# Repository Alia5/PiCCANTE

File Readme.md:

<br />

[![Discord](https://img.shields.io/discord/368823110817808384?logo=discord&logoColor=white&label=Discord&color=%23535fe5
)](https://discord.gg/hs34MtcHJY)

# PiCCANTE 🌶️

**Pi**CCANTE **C**ar **C**ontroller **A**rea **N**etwork **T**ool for **E**xploration

PiCCANTE is a powerful hacking tool for accessing, exploring, and manipulating vehicle CAN bus networks, built on the affordable Raspberry Pi Pico platform. Designed for researchers, security professionals, and automotive enthusiasts looking to dive deep into vehicle systems without expensive proprietary equipment.

⚠️ **Always exercise caution when connecting to vehicle systems.** ⚠️ 

## ℹ️ About PiCCANTE

PiCCANTE is designed to be a dead-**simple**, dirt-**cheap**, and readily-**available** hardware platform for vehicle research and exploration.  
As cars become more and more computerized, manufacturers keep locking them behind proprietary tools and restrictive systems, even connect vehicles to the internet, yet they still rely on communication standards from the 1980s.  
Car hacking and independent research grows increasingly important to discover security vulnerabilities, reverse engineer vehicle systems, and empower owners with custom tools for diagnostics and tuning that support the Right to Repair movement.

The project leverages Raspberry Pi Pico (2 [W]) development boards, selected for their exceptional affordability, global availability, impressive specifications, and well-documented open-source SDK.

### 🎯 Core Goals

<sub>Keep it D.I.R.T.Y 😉</sub>  

- **D**ead-Simple 🔨  
  - Simple enough for perfboard soldering with minimal components. (Proper PCB available!)
  - No fiddling around with compilers and SDKs: Pre-built firmware releases for immediate use.
- **I**nexpensive 💰  
  - Minimal hardware requirements to keep costs dirt-cheap.  
  - Based on affordable, off-the-shelf components.
- **R**eadily-Available 🌎
  - Fully open-source hardware and software.  
  - Uses widely available Raspberry Pi Pico boards.
- **T**ool-Compatible 🔌
  - Seamless integration with existing CAN tools.  
- **Y**our-First Choice 💡
  - Driverless across all major operating systems.  
  - Easy to use for beginners and experts alike.
  - 🔜 Documentation

### ✨ Features

- ✅ Up to 3× CAN 2.0B interfaces (2× on RP2040 (Pico[W]), 3× on RP2350 (Pico 2[W]))
- ✅ 1× USB-CDC PiCCANTE command + GVRET (binary only) interface
  - Compatible with [SavvyCAN](https://github.com/collin80/SavvyCAN) and other automotive tools
- ✅ Up to 3× USB-CDC SLCAN interfaces (dedicated to each CAN channel)
  - SocketCAN compatible via [can-utils (Linux)](https://github.com/linux-can/can-utils)
- ✅ LED status indicators
- ✅ Command line interface for configuration and diagnostics
- ✅ Auto (Deep) sleep on idle + Wakeup on CAN activity.
- ✅ WiFi support (on Pico W models)
  - ✅ Create WiFi access point (`wifi ap <ssid> <password> <channel>`)
  - ✅ Connect to existing WiFi networks (`wifi connect <ssid> <password>`)
  - ✅ WiFi status and configuration commands
  - ✅ PiCCANTE configuration + GVRET interface as Telnet server
- ✅ Web-based configuration interface (on Pico W models)
  - ✅ Fully responsive on desktop and mobile
  - ✅ Full device configuration
  - ✅ Device Monitoring
  - 🔜 Integrated Web CLI:  
    - 🔜 Live CAN-bus monitoring
    - 🔜 ELM327 commands
  - 🔜 MITM mode configuration
- ✅ Bluetooth support (on Pico W models)
- ☑️ (partial) ELM327 emulator
  - ☑️ Partially implemented AT command set
    - Setup up CAN bus, auto protocol detection and filters (🔜) are missing.  
      Configure the CAN bus beforehand - this is a hacking-tool, you should now your vehicles CAN bus settings.
  - ✅ Support for USB, Bluetooth or WiFi communication
  - ✅ PID request and response
    - ✅ 11bit and 29bit addressing
    - ✅ Multi-Frame PID support (ISO-TP)
    - ✅ Fast mode when number of answered frames is known
  - ✅ Report vehicle battery voltage (if ADC is connected)
  - 🔜 Adaptive Timeouts
- ✅ 3D printable case designs for creating PiCCANTE based OBD-II dongles
- 🔜 Data logging to SD card
- 🔜 MITM mode for advanced analysis / vehicle tuning
- 🔜 (Software) CAN filters

## 🔧 Hardware

For more information, checkout the [hardware](./hardware) directory.

### Simplest version

PiCCANTE is designed to be modular and can be built with just a few components.  
The simplest version just uses a Pico board and a CAN transceiver.

### 🛒 What You'll Need

- 1× Raspberry Pi Pico (any model, RP2040 or RP2350)
  - **Note:** The Pico 2 W (RP2350) is recommended for full feature support, including WiFi and Bluetooth.
- 1-3× CAN transceivers (readily available SN65HVD or any other 3.3V compatible transceiver)
  - **Note:** ⚠️ Most readily available transceiver breakout-boards have a 120 Ohm terminating Resistor on them, when connecting to an existing (terminated) CAN bus this **needs** to be removed. ⚠️
- USB cable

If you want more features, you can add an SD card slot, a buck converter, and other things.

<details>
  <summary>Show Details</summary>
  <br />

</details>

### OBD-II Dongle (DIY Perfboard)

A full PiCCANTE based OBD-II dongle is simple enough to be soldered onto double-sided perfboard.

<details>
  <summary>Show Details</summary>
<br />

A perfboard version fits on a 60mm x 50mm board and the 3D printable case measures just 97mm x 56mm including the OBD-II connector.

It cam be built with the following components (but you can omit anything you don't need):

- Pi Pico (2 [W])
- 3x CAN transceivers (eg. SN65HVD, any 3.3V compatible transceiver will do)
- buck-converter
- SD card slot
- Voltage divider for measuring the vehicle's battery voltage
- Schottky diode for safe dual power supply (1N5817)
- **Case**:
  - ABS/ASA or PETG filament
  - 3x M3 screws
  - 3x M3 heatset inserts
  - 1x male OBD-II connector (I used [this one](https://store.minitools.com/en/components-and-connectors/obd-connectors/sep-a-obd-e2-obd2-male-connector.html))
  - Wires

</details>

### OBD-II Dongle (Manufactured PCB)

A proper PCB with better CAN transceivers can be found in the [hardware directory](./hardware/PiCCANTE-OBD-Dongle/PCB).  
It is made with [KiCAD](https://www.kicad.org/) and can be manufactured by any PCB manufacturer.

<details>
  <summary>Show Details</summary>
    <br />

</details>

## 💾 Software

Pre-compiled binaries for all official Raspberry Pi Pico boards are available as CI action artifacts in the GitHub repository.

When connected via USB, PiCCANTE exposes **up to** 4× USB-CDC interfaces:

- 1× Combined PiCCANTE command + GVRET (binary) interface
  - Always the _first_ exposed CDC device.
  - Also exposed via telnet if enabled on WiFi enabled boards.
- **Up to** 3× SLCAN interfaces (dedicated to each CAN channel)

### 🚀 Basic Usage Examples

#### 🐧 Linux with can-utils (slcan)

```bash
# Set up SLCAN interface
sudo slcand -o -s6 -t hw -S 3000000 /dev/ttyACM1 can0
sudo ip link set up can0

# Monitor CAN traffic
candump can0
```

#### 🖥️ Cross Platform with SavvyCAN

1. Connect PiCCANTE to USB
2. Open SavvyCAN
3. Go to Connection ➡️ Open Connection Window ➡️ Add device Connection
4. Select "Serial Connection (GVRET)" and choose the appropriate COM port / TTY
5. Click "Create New Connection"

### ⌨️ PiCCANTE Commands

```
atz             - Enable ELM mode (if ELM327-Emulator is on USB)
binary          - Toggle GVRET binary mode (binary <on|off>)
can_bitrate     - Change CAN bus bitrate (can_bitrate <bus> <bitrate>)
can_disable     - Disable CAN bus (can_disable <bus>)
can_enable      - Enable CAN bus with specified bitrate (can_enable <bus> <bitrate>)
can_status      - Show status of CAN buses
echo            - Toggle command echo (echo <on|off>)
elm             - Configure ELM327 interface and mode (elm <usb|bt PIN|wifi>  <can0|can1|can2>)
help            - Display this help message
idle_timeout    - Set idle timeout in minutes (idle_timeout disable|<minutes>)
led_mode        - Set LED mode (led_mode <0-3>) 0=OFF, 1=Power, 2=CAN Activity
log_level       - Set log level (log_level <0-3>). 0=DEBUG, 1=INFO, 2=WARNING, 3=ERROR
reset           - Reset the system (reset)
save            - Save current settings to flash
set_num_busses  - Set number of CAN buses (can_num_busses [number])
settings        - Show current system settings
sleep           - Enter deep sleep mode (sleep)
sys_stats       - Display system information and resource usage (sys_stats [cpu|heap|fs|tasks|uptime|adc|wifi])
telnet          - Enable or disable Telnet and set port (telnet enable|disable | telnet <port
version         - Display version information (version)
wifi            - Manage WiFi settings (wifi info | wifi connect <ssid> <password> | wifi ap <ssid> <password> <channel> | wifi disable)
```

## ❓ Frequently Asked Questions

### 🔄 Why only CAN2.0B and not CAN FD/XL?

The Raspberry Pi Pico has no native CAN support. The PIO can2040 implementation we're using only supports CAN 2.0B (due to licensing issues).  
However, if you **need** CAN FD or other bus types, feel free to open a PR supporting a CAN controller (like MCP2518FD).  

### 🔌 Can I use PiCCANTE with Linux/Windows/macOS?

Yes! PiCCANTE is designed to be cross-platform. It works with any operating system as a standard USB device with no special drivers required.  
For SLCAN interfaces, Linux users can use can-utils to provide a SocketCAN interface, while all platforms support the GVRET/SLCAN interface through tools like SavvyCAN.

### 💻 How many CAN buses can I monitor simultaneously?

Up to 3 CAN buses on the RP2350 (Pico 2/2W) and up to 2 CAN buses on the RP2040 (original Pico/Pico W).  
Each bus has a dedicated USB-CDC SLCAN interface.

### 🔧 Why build my own instead of buying a commercial CAN adapter?

PiCCANTE gives you a fully open-source solution at a fraction of the cost of commercial tools.  
You get complete control over the hardware and software, the ability to customize for specific needs, and valuable learning experience about CAN networks and embedded systems.

## ❓ Troubleshooting

- **Issue**: CAN bus not receiving data  
  *Solutions*:  
  - Verify CAN status with `can_status` command
  - Verify wiring and bitrate settings
  - Check for proper bus termination resistance (remove resistor on the transceiver if connected to an existing CAN-bus)

- **Issue**: LED not lighting up / blinking  
  *Solutions*:
  - Check USB connection and power
  - Check led_mode command on the first USB CDC device

## 🛠️ Development

PiCCANTE is built using the Raspberry Pi Pico SDK and follows standard Pico development practices. This section covers how to set up your development environment, build the project, and extend its functionality.

### 🧰 Prerequisites

- [Raspberry Pi Pico SDK](https://github.com/raspberrypi/pico-sdk)
- [CMake](https://cmake.org/) (3.13 or newer) [Windows: bundled with PicoSDK]
- C/C++ compiler (GCC ARM) [Windows: bundled with PicoSDK]
- [Visual Studio Code](https://code.visualstudio.com/) with the [Pico extension]([https://marketplace.visualstudio.com/items?itemName=marus25.cortex-debug](https://marketplace.visualstudio.com/items?itemName=raspberry-pi.raspberry-pi-pico)) (recommended)

### 🔄 Environment Setup

1. **Install the Pico SDK**:

    Follow the instructions in the [Pico SDK documentation](https://github.com/raspberrypi/pico-sdk) to install the SDK

2. **Clone PiCCANTE**:

    ```bash
    git clone git@github.com:Alia5/PiCCANTE.git
    cd PiCCANTE
    git submodule update --init --recursive
    ```

### 🏗️ Building

#### 💻 Command Line

1. **Configure with CMake**:

   ```bash
   cmake -B build -G Ninja -DCMAKE_BUILD_TYPE=Release
   ```

2. **Build the project**:

   ```bash
   cmake --build build --config Release
   ```

#### 🖥️ Using VS Code

1. Open the PiCCANTE folder in VS Code
2. Press F1 and select "CMake: Configure"
3. Press F7 to build the project
4. To flash, connect a Pico in BOOTSEL mode and press F5

## 👥 Contributing

Contributions to PiCCANTE are welcome! Whether it's bug reports, feature requests, documentation improvements, or code contributions, your help makes this project better.

- **Bug Reports**: Open an issue describing the problem and steps to reproduce it
- **Feature Requests**: Open an issue describing the desired functionality
- **Code Contributions**: Fork the repository, make your changes, and submit a pull request

### Extending PiCCANTE

PiCCANTE is designed to be extensible. Here are some key areas where you might want to extend functionality:

- **Adding new commands**: Extend the command interpreter to add custom commands.
- **Implementing new protocols**: Add new protocol handlers in their respective directories.
- **Car-specific tools**: Fork PiCCANTE to create a car-specific tool and diagnostics dongle.
- **Custom gauges**: Fork PiCCANTE and use it as a base controller to implement custom gauges.
- **Custom data logging**: Implement custom data logging to SD card to monitor your vehicle on a track day.

## 📄 License

```
PiCCANTE - PiCCANTE Car Controller Area Network Tool for Exploration
Copyright (C) 2025 Peter Repukat

This program is free software: you can redistribute it and/or modify
it under the terms of the GNU General Public License as published by
the Free Software Foundation, either version 3 of the License, or
(at your option) any later version.

This program is distributed in the hope that it will be useful,
but WITHOUT ANY WARRANTY; without even the implied warranty of
MERCHANTABILITY or FITNESS FOR A PARTICULAR PURPOSE.  See the
GNU General Public License for more details.

You should have received a copy of the GNU General Public License
along with this program.  If not, see <https://www.gnu.org/licenses/>.
```

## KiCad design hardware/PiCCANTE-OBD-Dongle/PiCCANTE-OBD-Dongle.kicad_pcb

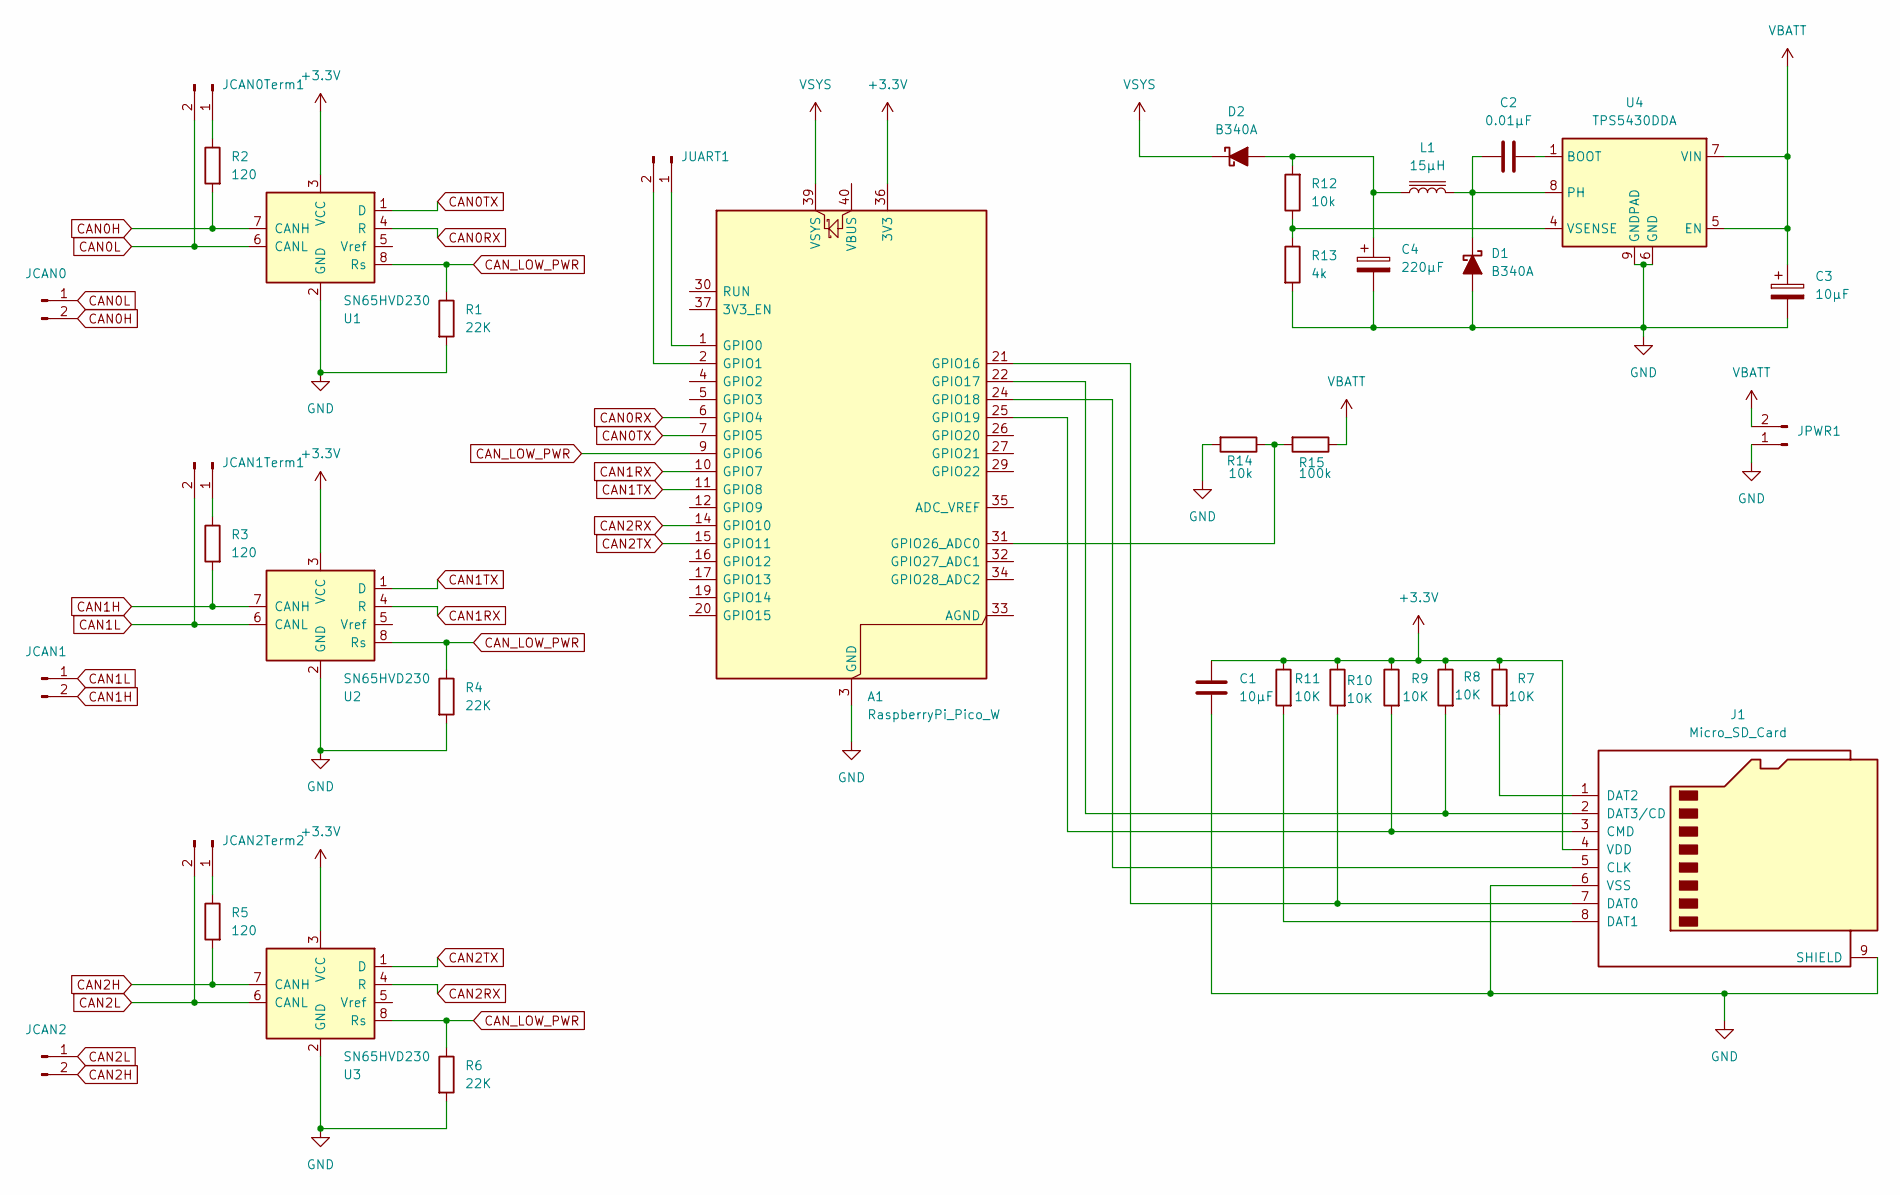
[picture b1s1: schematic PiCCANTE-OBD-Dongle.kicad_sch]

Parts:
A1: RaspberryPi_Pico_W; RaspberryPi_Pico_W_SMD_HandSolder_CUSTOM_KEEPOUT
C1: 10µF; C_0201_0603Metric
C2: 0.01µF; C_0201_0603Metric
C3: 10µF; CP_Elec_4x5.4
C4: 220µF; CP_Elec_6.3x5.4_Nichicon
D1, D2: B340A; SMA_L4.4-W2.6-LS5.0-RD
J1: Micro_SD_Card; TF-SMD_503398-1892
JCAN0, JCAN1, JCAN2: PinHeader_1x02_P2.54mm_Horizontal
JCAN0Term1, JCAN1Term1, JCAN2Term2: PinHeader_1x02_P2.54mm_Vertical
JPWR1: PinHeader_1x02_P2.54mm_Horizontal
JUART1: PinHeader_1x02_P2.54mm_Vertical
L1: 15µH; L_6.3x6.3_H3
R1, R4, R6: 22K; R_0201_0603Metric
R2, R3, R5: 120; R_0201_0603Metric
R7, R8, R9, R10, R11: 10K; R_0201_0603Metric
R12, R14: 10k; R_0603_1608Metric
R13: 4k; R_0603_1608Metric
R15: 100k; R_0603_1608Metric
U1, U2, U3: SN65HVD230; SOIC-8_3.9x4.9mm_P1.27mm
U4: TPS5430DDA; TI_SO-PowerPAD-8_ThermalVias

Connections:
+3.3V: A1.36 (3V3), C1.1, J1.4 (VDD), R7.1, R8.1, R9.1, R10.1, R11.1, U1.3 (VCC), U2.3 (VCC), U3.3 (VCC)
CAN0H: JCAN0.2, R2.1, U1.7 (CANH)
CAN0L: JCAN0.1, JCAN0Term1.2, U1.6 (CANL)
CAN0RX: A1.6 (GPIO4), U1.4 (R)
CAN0TX: A1.7 (GPIO5), U1.1 (D)
CAN1H: JCAN1.2, R3.1, U2.7 (CANH)
CAN1L: JCAN1.1, JCAN1Term1.2, U2.6 (CANL)
CAN1RX: A1.10 (GPIO7), U2.4 (R)
CAN1TX: A1.11 (GPIO8), U2.1 (D)
CAN2H: JCAN2.2, R5.1, U3.7 (CANH)
CAN2L: JCAN2.1, JCAN2Term2.2, U3.6 (CANL)
CAN2RX: A1.14 (GPIO10), U3.4 (R)
CAN2TX: A1.15 (GPIO11), U3.1 (D)
CAN_LOW_PWR: A1.9 (GPIO6), R1.1, R4.1, R6.1, U1.8 (Rs), U2.8 (Rs), U3.8 (Rs)
GND: A1.3 (GND), A1.8 (GND), A1.13 (GND), A1.18 (GND), A1.23 (GND), A1.28 (GND), A1.38 (GND), C1.2, C3.2, C4.2, D1.2 (A), J1.6 (VSS), J1.9 (SHIELD), JPWR1.1, R1.2, R4.2, R6.2, R13.2, R14.2, U1.2 (GND), U2.2 (GND), U3.2 (GND), U4.6 (GND), U4.9 (GNDPAD)
unnamed: A1.1 (GPIO0), JUART1.1
unnamed: A1.2 (GPIO1), JUART1.2
unnamed: A1.21 (GPIO16), J1.7 (DAT0), R10.2
unnamed: A1.22 (GPIO17), J1.2 (DAT3/CD), R8.2
unnamed: A1.24 (GPIO18), J1.5 (CLK)
unnamed: A1.25 (GPIO19), J1.3 (CMD), R9.2
unnamed: A1.31 (GPIO26_ADC0), R14.1, R15.2
unnamed: C2.2, D1.1 (K), L1.2, U4.8 (PH)
unnamed: C4.1, D2.2 (A), L1.1, R12.2
unnamed: J1.8 (DAT1), R11.2
unnamed: J1.1 (DAT2), R7.2
unnamed: JCAN0Term1.1, R2.2
unnamed: JCAN1Term1.1, R3.2
unnamed: JCAN2Term2.1, R5.2
unnamed: C2.1, U4.1 (BOOT)
unnamed: R12.1, R13.1, U4.4 (VSENSE)
VBATT: C3.1, JPWR1.2, R15.1, U4.5 (EN), U4.7 (VIN)
VSYS: A1.39 (VSYS), D2.1 (K)

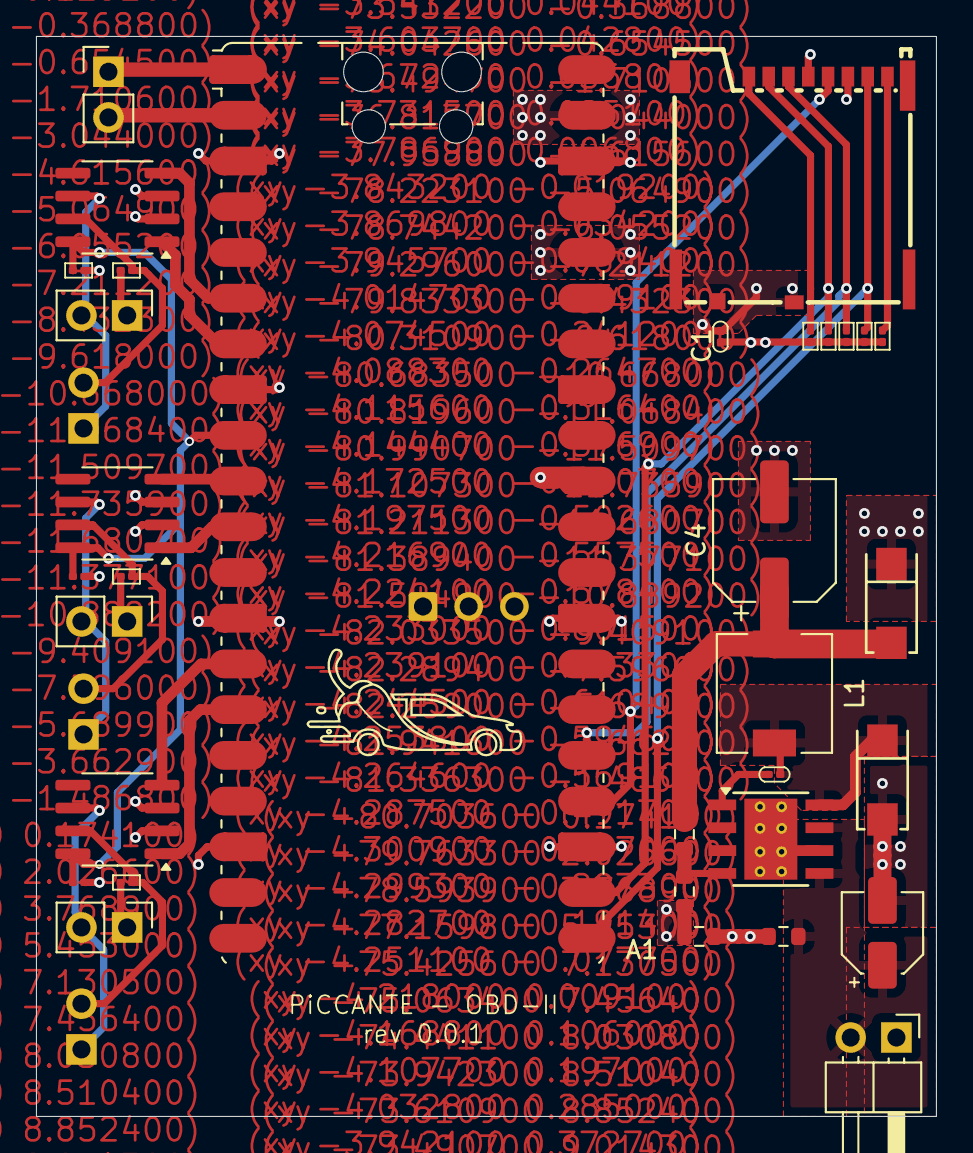
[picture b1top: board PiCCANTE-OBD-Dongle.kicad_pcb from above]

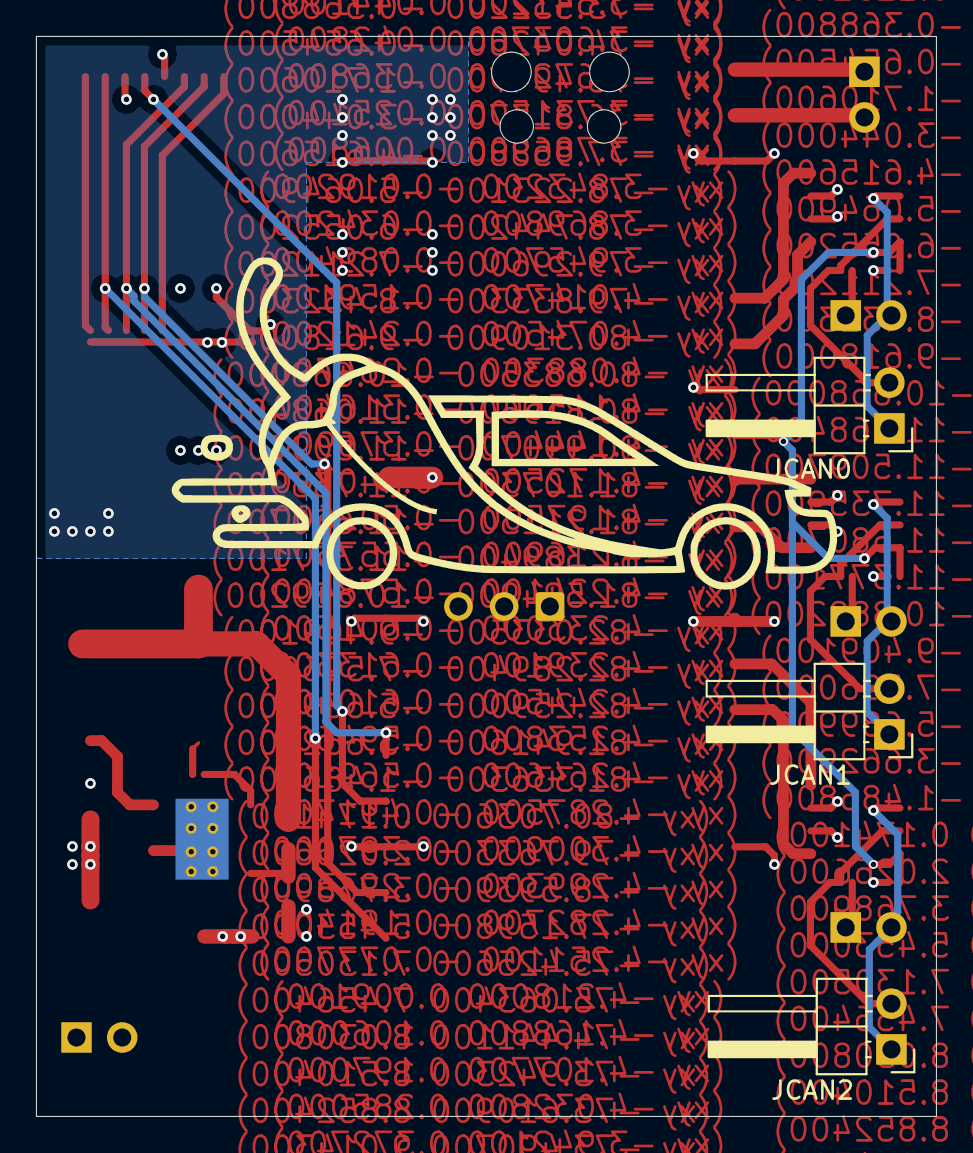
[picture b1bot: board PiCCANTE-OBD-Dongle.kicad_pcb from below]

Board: 4 copper layers, 50.0 x 60.0 mm, 36 parts (3 on the bottom side), 33 nets.

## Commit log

2025-03-29 Setup FreeRTOS
2025-03-29 Somewhat reliable debugging
2025-03-29 RuntimeStats
2025-03-30 Working CanBus Sample on FreeRTOS
2025-03-30 working-minimum-can-sample
    NOTE: Connect TO GPIO NUMBERS! NOT physical pins
2025-03-30 Add preliminary Logger
2025-03-30 Misc: Vscode stuff
2025-03-30 Add Preliminary CanBus abstraction
2025-03-30 Add WIP Lawicel protocol implementation
2025-03-30 Cleanup
2025-03-30 Add missing LICENSE.txt
2025-03-31 switch to pico 2 w
2025-03-31 Add generic ostream impl
2025-04-01 Change to own fork of can2040
2025-04-05 Move Lawicel-Proto dir
2025-04-05 Add .clang-tidy file
2025-04-05 Disable stdout to usb cdc 0
2025-04-05 remove cmsis dep
2025-04-05 Disable warnings for extlibs
2025-04-05 disable clang-tidy check in extlibs
2025-04-05 make clang-tidy happier
2025-04-05 Add gvret protocol impl. :)
2025-04-05 Add Readme.md
2025-04-05 Add License and copyright info
2025-04-05 Rename Project: PicoRET -> PiCCANTE
2025-04-05 Fix stupid broken vscode-native clang-tidy with c++23
2025-04-05 Refactor: wrap in namespace piccante
2025-04-05 Rework CanBus abstraction
2025-04-05 Env configurable pico board/platform
2025-04-05 Pull in littlefs
2025-04-05 Fix Logger spamming log tag multiple times per line
2025-04-05 Add little-fs driver w/ pre built and in-elf little-fs image 🤘
2025-04-05 Let clang-tidy do it's thing
2025-04-05 gvret::states: update license notice
2025-04-06 auto download mklittlefs
2025-04-06 update snapshot name
2025-04-06 make build cross platform compatible (hopefully)
2025-04-06 Remove std::XYZstream and pico/stdio bloat
2025-04-06 persistent canbus settings
2025-04-06 Fix default canbus nums
2025-04-06 completely disable/remove pico/stdio uart
2025-04-06 Fix littlefs driver
2025-04-06 increase littlefs image to 64kB
2025-04-06 Disable compiler warnings for sdk-files and libs
2025-04-06 ci: build for both pico_w and pico2_w
2025-04-06 speedup pipeline
2025-04-07 Bin2c.cmake: Trick the linker into showing the actual used size of the file-system partition
2025-04-07 use single sink for logging
2025-04-07 Clear a few compiler warnings
2025-04-07 Clean up lawicel handler
2025-04-07 Fix canbus number ifdefs
2025-04-07 Fix lawicell autopoll / start in autopoll mode
2025-04-07 Split "debug" tasks
2025-04-08 Refactor: Rename CAN_IDLE_SLEEP_MS -> IDLE_SLEEP_MS
2025-04-12 Pull in TinyUSB from source
2025-04-12 Fix stream sending 0 bytes for strings
2025-04-12 set CAN interrupts on core two
2025-04-12 Fix canbus reset issues
2025-04-12 Rename Lawicel -> SLCAN / CLeanup SLCAN
2025-04-12 GVRET time using micros
2025-04-12 Generate as many cdc interfaces as slcan devices +1
2025-04-13 Bring back GVRET handler and introduce piccante sys_shell
2025-04-13 Add system monitor and commands
2025-04-13 Add littlefs stats
2025-04-13 Init cyw43 on supported boards / add LED toggle
2025-04-13 CI: Build variants for non "w" boards
2025-04-13 Add Code of Conduct
2025-04-13 Add PR and Issue templates
2025-04-13 Add led mode command
2025-04-13 Add reset command
2025-04-13 Fix LED init when on non W board
2025-04-13 Fix typo
2025-04-14 Add ADC to stats
2025-04-14 Change WiFi Hostname
2025-04-14 Add Basic WiFi and commands
2025-04-14 Fix non W builds
2025-04-14 Add GitHub Sponsors buttons
2025-04-14 Add Telnet PiCCANTE+GVRET
2025-04-14 Make WiFi connection command more responsive and cancellable
2025-04-14 Change default telnet port since SavvyCAN required it on 23 🙄
2025-04-14 Try to speed up telnet
2025-04-14 Fix build
2025-04-14 Fix: Blocking when USB-CDC port is not read
2025-04-14 Speed up telnet
2025-04-14 add cpu_total option to sys_stats
2025-04-14 Speedup telnet
2025-04-14 Fix GVRET interfering with piccante_cmd handler
2025-04-15 Add QA section to Readme.md
2025-04-15 Add TODO
2025-04-15 Pull in pico-extras
2025-04-15 Add basic sleep command
2025-04-15 Add auto sleep on no can-activity with configurable timeout
2025-04-15 Add missing settings to settings cmd
2025-04-15 Update pipelines
2025-04-16 Fix Idle Timer
2025-04-16 Fix GVRET CAN frame/keepalive interleave
2025-04-18 Add Preliminary WebUI
2025-04-18 Prefer fs_files.local
2025-04-18 Web: use gzip instead of brotil
2025-04-18 W Boards: Add httpd
2025-04-19 Bundle web-assets automagically on w boards
2025-04-20 Fix setting led_mode
2025-04-20 Add settings http-endpoints
2025-04-20 Add settings-save (and reset) endpoint
2025-04-20 Fix sending null term byte in json
2025-04-20 Properly format response headers
2025-04-20 Web: Partially impl. get settings
2025-04-20 Web: Clear outdir on build
2025-04-20 misc: disable vscode formatOnSave for ts/js/svelte (let linter handle it)
2025-04-20 Fix fmt adding 0 term to std::stirngs
2025-04-20 Add can settings to /api/settings endpoint (GET)
2025-04-20 Fix wake_up from idle timer
2025-04-20 misc: vscode
2025-04-20 /api/settings: set can props from api
2025-04-20 Add missing listen_only to (can) /api/settings
2025-04-20 Fix disabled css
2025-04-20 Dropdown: add disable flag
2025-04-20 Web: Settings read all from api
2025-04-20 Fix json parsing
2025-04-20 Immediately apply most settings via API
2025-04-20 misc: vscode...
2025-04-20 Web: Complete settings page
2025-04-20 Apply WiFi Settings on (API) settings-change
2025-04-20 change usb descriptor w/ user configurable number of can-interfaces
2025-04-21 Rebuild little-fs image only on clean builds
2025-04-21 Introduce versioning
2025-04-21 Add about endpoint
2025-04-21 Web: Add about page
2025-04-21 Misc: include license headers
2025-04-21 Rework CPU/Task stats
2025-04-21 Add stats http endpoint
2025-04-22 Fix stats API malformed json
2025-04-22 Start working on stats page
2025-04-22 CPU/Task-Stats
2025-04-22 Sort Tasks by usage
2025-04-22 Fix blank spaces in logo
2025-04-22 Reduce web bundle size a bit
2025-04-22 Add CanBus Stats
2025-04-22 Double CanQueue Size
2025-04-22 Fix Masonry transitions
2025-04-22 Improve CAN-stats look on wide screens
2025-04-22 Inset inner card shadows
2025-04-22 Support multiple telnet servers
2025-04-23 Add completely untested ELM327 Emulator
2025-04-23 SLCAN: allow arbitrarily large commands
2025-04-23 Wifi: Add missing dhcp_server
2025-04-23 http-server: remove hostname check
2025-04-23 Fix stats init
2025-04-23 Fix passing elm_params by copy
2025-04-23 Optimize CAN RX task a tiny bit
2025-04-23 Remove core affinity for CAN RX
2025-04-23 Optimize unread usb-cdc- stream a bit (still a hack)
2025-04-23 Fix init/wake_up if there are comms on the bus
2025-04-24 Send GVRET Keepalive all at once
2025-04-24 Fix changing Idle timeout
2025-04-24 Hopefully fix possible crash upon going to sleep
2025-04-24 Add can overflow stats to gui
2025-04-24 Increase CAN RX task performance a bit
2025-04-24 better handle unread usb-cdcs
2025-04-24 Fixup can performance
2025-04-24 Greatly increase CAN RX Task performance
    - Setting led state can take a long time on W board (spi via cyw43 chip)
    Replaced with simple bool flag and separate blink task
    - Resetting timers can cause significant delay
    Replaced with simple bool flag checked in idle-detect task
2025-04-24 Hopefully fix ELM timeout logic
2025-04-24 Adjust ELM defaults
2025-04-24 Prevent too low timeouts to be set
2025-04-24 Fix ELM Descriptions
2025-04-24 ELM: Fix(???) end_ok(????)
2025-04-24 Fix ELM327 Comunication
    Holy fucks... First byte is omitted because it is DLC?!
2025-04-24 Decrease LED Blink-TaskStacksize
2025-04-24 Increase Heap on RP2350
2025-04-24 Fix ELM327-Emulator adaptive timing
2025-04-24 Adjust ELM327 Timeout logic...
2025-04-25 Adjust Canbus delay logic
2025-04-25 Adjust ELM327 Timeouts, again
2025-04-25 "Proper" ELM327 Timeouts
2025-04-25 Elm327: support/handle "expected number of frames" in pid requests
2025-04-25 ELM327 Fix headers/ids when using extended addressing
2025-04-25 ELM327 Add mutex to writes
2025-04-25 inline hex util
2025-04-25 Fix: possibly sending wrong data length to elm
2025-04-26 Refactor
2025-04-26 Desperate attempts at getthing ELM emu to work reliably.
2025-04-26 Put ELM327-Emu on Bluetooth.
2025-04-26 Try to fix some random btstack crash
2025-04-26 Update ELM emulator timeout handling, again
2025-04-27 WIP: ELM: Multi Frame messages
2025-04-27 ELM327: Add flow control
2025-04-27 Amend me: Perf
2025-04-27 Rework BT.
    Fixes crashes, get's rid of falsy implemented bt loop (is part of async_context_t when using cyw_arch_freertos_blahblah)
2025-04-27 Increase BT / ELM327 performance a bit
2025-04-27 Safely read VSYS Adc on PicoW
2025-04-27 ELM: support requesting multiple pids at once.
2025-04-27 Revert "ELM: support requesting multiple pids at once."
    This reverts commit 3f4be84fd427f070ba9c60f0056e4937f5ba5a88.
2025-04-28 support longer pid requests
2025-04-28 ELM Fix adaptive timing resetting timeout value
2025-04-28 ELM: Fix multi frame responses / remove adaptive timeout for now
2025-04-28 Significantly improve telnet server speed
2025-04-28 Sys-Shell: ignore null bytes
2025-04-28 Temporarily move ELM emulator to WIFI
2025-04-28 Fix spotty telnet
2025-04-28 AMEND_ME
2025-04-28 Fix Slow canbus send
2025-04-28 ELM: Fix multi-frame pids
2025-04-28 ELM: stub commands required for some diagnosis-tools (AlfaOBD)
2025-04-28 ELM: automagically set usage of extended frame when setting extended header
2025-04-29 Optimize memory usage a bit
2025-05-01 Configurable ELM emulator
2025-05-01 Add ELM emulator settings to webinterface
2025-05-01 Support setting ELM Emulator settings via WebInterface
2025-05-01 Update pipeline
2025-05-01 (Re-)Disable printf to uart
2025-05-01 Add watchdog to recover from FW-crashes
2025-05-02 Fix crash on high can activity
2025-05-02 Fix watchdog interferring with debugger
2025-05-02 Clear up some performance issues
2025-05-02 Add very basic SD-Card support
2025-05-03 Add HW Schematic / Images
2025-05-03 Perfobaord image: Fix missing Pico
2025-05-03 Fix typos
2025-05-03 Update Perfboard-Bottom Image
2025-05-03 Add 3D printed case
2025-05-03 Fix hardware oopsie
2025-05-03 Add theoretical support to power / up/down can transceivers
2025-05-03 Update default pin values
2025-05-03 Adjust ADC0 Voltage multiplier
2025-05-03 Delay start of BT-Task a tad
2025-05-03 Fix canbus-settings over api
2025-05-03 ELM-Emu: Report voltage via ADC
2025-05-03 Add release workflwo
2025-05-10 Provide and use own CanFrame struct
2025-05-10 Put pico on the other side
2025-05-10 Add custom pcb design
2025-05-10 Switch out TRX / "Improve" Routing
2025-05-10 Fix missing pragma pack on wifi settings
2025-05-10 Add can speed lock setting
    Prevents GVRET / SLCAN interfaces from changing CAN bus speed
    Changelog: feature
2025-05-10 Add autogenerated changelog to releases
2025-05-10 Add CAN bridge
    Changelog: feature
2025-05-10 Update Changelog generate
2025-05-24 Fix littlefs driver SMP
2025-05-24 Fix Can queues
2025-05-24 Fix sd-card init fail returning no error
2025-05-24 Add Case for manufactured PCB
2025-05-24 FIXME: Add low power output for ca trx on pcb
2025-05-24 Update deps
2025-05-25 Fix GVRET only exposing CAN0
    Changelog: fix
2025-05-25 Make CAN2 read only on W boards...
2025-05-25 Use single callback for all can buses
2025-05-25 Fix can pin assignments
2025-05-28 Fix crash when WiFi not possible
2025-05-28 Reserve PIOs for CanBuses - Leaving 2 free if bus is read_only
2025-09-25 Fixed generate_littlefs.cmake for Mac (build failed pulls Linux bins)
2025-09-26 added pico-sdk to submodules
2025-12-19 Workflow Dispatch testing

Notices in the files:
Readme.md:
License: GPL-3.0
